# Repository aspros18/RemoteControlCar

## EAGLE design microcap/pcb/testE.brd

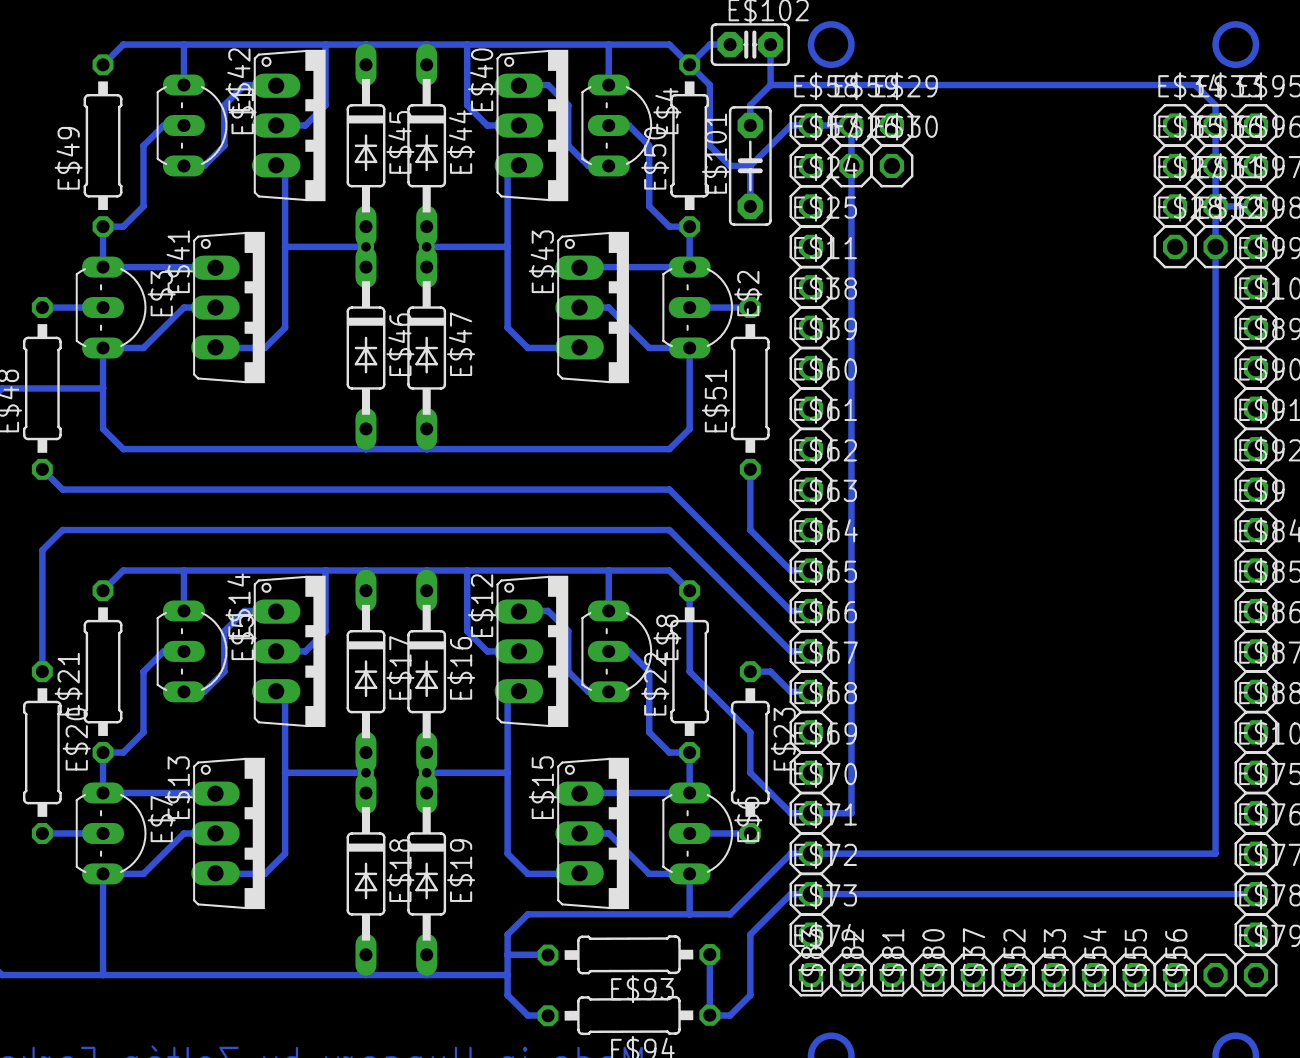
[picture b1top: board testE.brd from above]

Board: 2 copper layers, 102 parts (0 on the bottom side), 18 nets.

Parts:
E$1, E$2, E$3, E$4, E$5, E$6, E$7, E$8: TO92-CBE
E$9, E$10, E$11, E$24, E$25, E$26, E$27, E$28, E$29, E$30, E$31, E$32, E$33, E$34, E$35, E$36, E$37, E$38, E$39, E$52, E$53, E$54, E$55, E$56, E$57, E$58, E$59, E$60, E$61, E$62, E$63, E$64, E$65, E$66, E$67, E$68, E$69, E$70, E$71, E$72, E$73, E$74, E$75, E$76, E$77, E$78, E$79, E$80, E$81, E$82, E$83, E$84, E$85, E$86, E$87, E$88, E$89, E$90, E$91, E$92, E$95, E$96, E$97, E$98, E$99, E$100: 1X01
E$12, E$13, E$14, E$15, E$40, E$41, E$42, E$43: T-30_V
E$16, E$17, E$18, E$19, E$44, E$45, E$46, E$47: C2992
E$20, E$21, E$22, E$23, E$48, E$49, E$50, E$51, E$93, E$94: 0207/10
E$101: C5B2.5
E$102: C2.5-2

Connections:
S$2: E$2.C, E$4.B, E$50.1
S$5: E$3.B, E$48.2
S$6: E$2.B, E$51.2
S$7: E$5.B, E$7.C, E$21.1
S$8: E$2.E, E$3.E, E$6.E, E$7.E, E$18.A, E$19.A, E$46.A, E$47.A, E$71.1, E$97.1, E$101.2, E$102.2
S$9: E$1.B, E$3.C, E$49.1
S$12: E$17.A, E$18.C
S$15: E$23.1, E$67.1
S$16: E$6.C, E$8.B, E$22.1
S$17: E$6.B, E$23.2
S$19: E$16.A, E$19.C
S$20: E$51.1, E$64.1
S$21: E$7.B, E$20.2
S$22: E$45.A, E$46.C
S$23: E$48.1, E$65.1
S$25: E$44.A, E$47.C
S$28: E$1.C, E$4.C, E$5.C, E$8.C, E$16.C, E$17.C, E$21.2, E$22.2, E$44.C, E$45.C, E$49.2, E$50.2, E$58.1, E$59.1, E$70.1, E$101.1, E$102.1
S$36: E$20.1, E$66.1
